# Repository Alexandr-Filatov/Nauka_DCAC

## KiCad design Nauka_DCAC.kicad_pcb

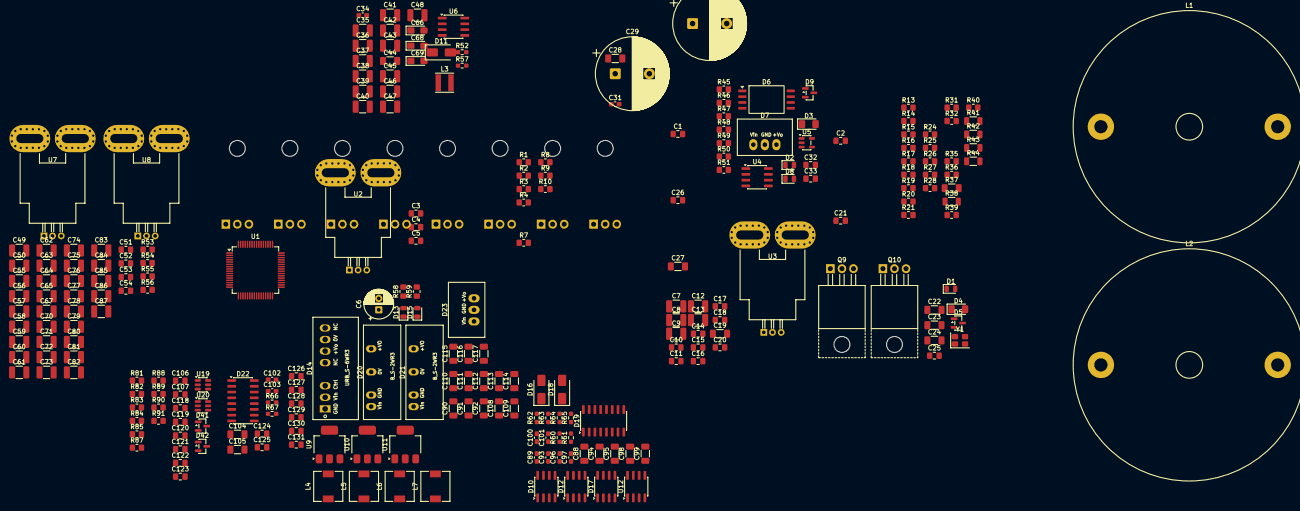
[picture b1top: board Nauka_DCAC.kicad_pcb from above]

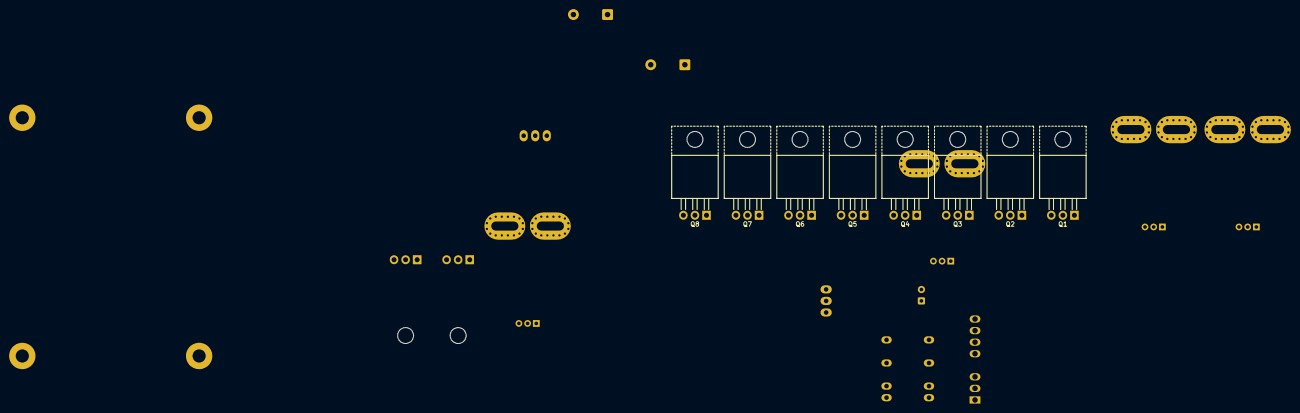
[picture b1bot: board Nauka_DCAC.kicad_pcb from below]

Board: 2 copper layers, 255 parts (8 on the bottom side), 101 nets, no tracks yet.

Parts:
C1, C2: 12p; C_0805_2012Metric_Pad1.18x1.45mm_HandSolder
C3, C11, C15, C18, C21, C32, C52, C54, C119, C121, C122, C123, C124, C125, C126, C127, C128, C129, C130, C131: 100n; C_0805_2012Metric_Pad1.18x1.45mm_HandSolder
C4, C5, C17, C20, C118, C120: 2.2u; C_0805_2012Metric_Pad1.18x1.45mm_HandSolder
C6: 47u; CP_Radial_D6.3mm_P2.50mm
C7, C8, C9, C12, C13, C35, C36, C37, C38, C39, C40, C41, C42, C43, C45, C46, C47, C48, C49, C50, C55, C56, C57, C58, C59, C60, C61, C62, C63, C64, C65, C67, C70, C71, C72, C73, C74, C75, C76, C77, C78, C79, C80, C81, C82, C83, C84, C85, C86, C87: 470n; C_1210_3225Metric_Pad1.33x2.70mm_HandSolder
C10, C14, C51, C53: 1u; C_0805_2012Metric_Pad1.18x1.45mm_HandSolder
C16, C25, C26: 56p; C_0805_2012Metric_Pad1.18x1.45mm_HandSolder
C19, C22, C44, C88, C90, C92, C94, C95, C98, C99, C104, C105, C108, C109, C110, C111, C112, C113, C114, C115, C116, C117: 10u; C_1206_3216Metric_Pad1.33x1.80mm_HandSolder
C23, C24, C27, C28: 2.2u; C_1206_3216Metric_Pad1.33x1.80mm_HandSolder
C29, C30: 1m; CP_Radial_D16.0mm_P7.50mm
C31, C34, C89, C93, C96, C97, C100, C101, C102, C103: 56p; C_0603_1608Metric_Pad1.08x0.95mm_HandSolder
C33: 1n; C_0805_2012Metric_Pad1.18x1.45mm_HandSolder
C66, C68, C69: 10u; CP_EIA-3216-18_Kemet-A_HandSolder
C91: 22u; C_1206_3216Metric_Pad1.33x1.80mm_HandSolder
C106, C107: 10p; C_0805_2012Metric_Pad1.18x1.45mm_HandSolder
D1, D2, D8, D13, D15: LED_0805_2012Metric
D3, D4: LED_1206_3216Metric_Pad1.42x1.75mm_HandSolder
D5, D9, D41, D42: SOT-23
D6: SOIC-8_7.5x5.85mm_P1.27mm
D7, D23: K78xx-500R3
D10, D12, D17: SOIC-8_3.9x4.9mm_P1.27mm
D11, D16, D18: D_SMA
D14: URB_S-6WR3
D19, D22: SOIC-16_3.9x9.9mm_P1.27mm
D20, D21: B_S-2WR3
L1, L2: L; L_Radial_D50.8mm_P38.86mm_Vishay_IHB-6
L3: 4.7u; L_Taiyo-Yuden_MD-4040
L4, L5, L6, L7: 10u; L_6.3x6.3_H3
Q1, Q2, Q3, Q4, Q5, Q6, Q7, Q8, Q9, Q10: TO-220-3_Horizontal_TabUp
R1, R2, R7, R8, R13, R14, R15, R17, R18, R24, R25, R28: 10k; R_0805_2012Metric_Pad1.20x1.40mm_HandSolder
R3, R4, R9, R10, R19, R20, R26, R27, R31, R32: 10; R_0805_2012Metric_Pad1.20x1.40mm_HandSolder
R16, R21, R46, R47, R48, R49, R58, R59, R84, R85, R90, R91: 1k; R_0805_2012Metric_Pad1.20x1.40mm_HandSolder
R35, R39, R53, R55: 2k; R_0805_2012Metric_Pad1.20x1.40mm_HandSolder
R36, R40, R54, R56: 3k; R_0805_2012Metric_Pad1.20x1.40mm_HandSolder
R37: 10k; R_1206_3216Metric_Pad1.30x1.75mm_HandSolder
R38, R41, R42, R43: 110k; R_1206_3216Metric
R44: 11.3k; R_1206_3216Metric
R45: 120; R_0805_2012Metric_Pad1.20x1.40mm_HandSolder
R50: 750; R_0805_2012Metric_Pad1.20x1.40mm_HandSolder
R51: 510; R_0805_2012Metric_Pad1.20x1.40mm_HandSolder
R52, R57, R60, R61, R62, R63, R64, R65, R66, R67: 120; R_0603_1608Metric_Pad0.98x0.95mm_HandSolder
R81, R87: 100; R_0805_2012Metric_Pad1.20x1.40mm_HandSolder
R82, R83, R88, R89: 0; R_0805_2012Metric_Pad1.20x1.40mm_HandSolder
U1: LQFP-64_10x10mm_P0.5mm
U2, U3, U7, U8: Allegro_CB_PFF
U4, U6, U12: SOIC-8_3.9x4.9mm_P1.27mm
U5: SOT-23-5
U9, U10, U11: SOT-223-3_TabPin2
U19, U20: SOT-23-6
Y1: 16M; Crystal_SMD_SeikoEpson_FA238-4Pin_3.2x2.5mm

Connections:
+3.3V: C20.2, C21.2, C32.1, C68.1, C118.1, C119.1, C120.1, C121.1, C124.2, C126.2, C128.2, C130.2, C131.2, D6.8 (VDD2), D9.2 (K), D15.2 (A), D19.1 (VDDI_1), D22.1 (DT_1), D41.2 (K), D42.2 (K), R28.1, R84.1, R90.1, U1.1 (VBAT), U1.13 (VDDA), U1.19 (VDD), U1.32 (VDD), U1.48 (VDD), U1.64 (VDD), U4.1 (VDD1), U5.5 (V+), U6.1 (VDD1), U10.2 (VO), U12.1 (VDD1), U19.4 (V+), U20.4 (V+)
+3.3VP: C17.2, C18.2, C69.1, C125.2, C127.2, C129.2, D5.2 (K), D6.1 (VDD1), D8.2 (A), U4.8 (VDD2), U6.8 (VDD2), U11.2 (VO), U12.8 (VDD2)
+5V: C10.1, C11.1, C14.1, C15.1, C51.1, C52.1, C53.1, C54.1, C66.1, D13.2 (A), U2.1 (VCC), U3.1 (VCC), U7.1 (VCC), U8.1 (VCC), U9.2 (VO)
+9V: C90.2, C92.2, D14.6 (+Vo), U9.3 (VI), U10.3 (VI)
+15V: C44.2, C94.2, C98.2, C109.2, D10.5 (VDD), D11.2 (A), D12.5 (VDD), D16.2 (A), D17.5 (VDD), D18.2 (A), D23.3 (+Vo)
+24V: C6.1, C23.2, C24.2, C27.2, C28.2, C29.1, C30.1, C110.1, C111.1, C112.1, C115.1, L1.2, L2.2, L3.1, L4.1, L5.1, L6.1, L7.1, R37.1, R38.2
/BOOT: R15.2, U1.60 (BOOT0)
/Drivers/A: C88.2, D10.6 (SW)
/Drivers/B: C95.2, D12.6 (SW)
/Drivers/C: C99.2, D17.6 (SW)
/NRST: C3.2, R28.2, U1.7 (NRST)
/OverCurrent1: C106.1, D41.3 (common), R81.1
/OverCurrent2: C107.1, D42.3 (common), R87.1
/Power/A: Q1.3 (S), Q2.2 (D), R1.2, U2.4 (IP+)
/Power/B: Q3.3 (S), Q4.2 (D), R7.2
/Power/C: Q5.3 (S), Q6.2 (D), R13.2, U3.4 (IP+)
/Power/Current_A: R35.2, R36.1
/Power/Current_C: R39.2, R40.1
/Power/Current_buck_1: R53.2, R54.1
/Power/Current_buck_2: R55.2, R56.1
/Power/DC+: C7.2, C8.2, C9.2, C12.2, C13.2, C35.2, C36.2, C37.2, C38.2, C39.2, C40.2, C41.2, C42.2, C43.2, C45.2, C46.2, C47.2, C48.2, C49.2, C50.2, C55.2, C56.2, C57.2, C58.2, C59.2, C60.2, C61.2, C62.2, C63.2, C64.2, C65.2, C67.2, C70.2, C71.2, C72.2, C73.2, C74.2, C75.2, C76.2, C77.2, C78.2, C79.2, C80.2, C81.2, C82.2, C83.2, C84.2, C85.2, C86.2, C87.2, Q1.2 (D), Q3.2 (D), Q5.2 (D), Q7.2 (D), Q8.2 (D)
/Power/GH1: Q1.1 (G), R1.1, R3.1
/Power/GH2: Q3.1 (G), R7.1, R9.1
/Power/GH3: Q5.1 (G), R13.1, R19.1
/Power/GH4: Q7.1 (G), R17.1, R26.1
/Power/GH4_ON: R26.2, R31.2
/Power/GH5: Q8.1 (G), R24.1, R31.1
/Power/GL1: Q2.1 (G), R2.1, R4.1
/Power/GL2: Q4.1 (G), R8.1, R10.1
/Power/GL3: Q6.1 (G), R14.1, R20.1
/Power/GL4: Q9.1 (G), R18.1, R27.1
/Power/GL5: Q10.1 (G), R25.1, R32.1
/Power/S1: Q7.3 (S), Q9.2 (D), R17.2, U7.4 (IP+)
/Power/S2: Q8.3 (S), Q10.2 (D), R24.2, U8.4 (IP+)
/Power/Voltage_MCU: C33.2, D9.3 (common), R51.2
/SHDN_OverCurrent_1: R82.2, U19.6 (SHDN)
/SHDN_OverCurrent_2: R88.2, U20.6 (SHDN)
GND: C1.1, C2.2, C3.1, C4.2, C5.2, C10.2, C11.2, C14.2, C15.2, C20.1, C21.1, C25.2, C32.2, C33.1, C51.2, C52.2, C53.2, C54.2, C66.2, C68.2, C90.1, C92.1, C100.2, C101.1, C102.2, C103.1, C106.2, C107.2, C118.2, C119.2, C120.2, C121.2, C122.2, C123.2, C124.1, C126.1, C128.1, C130.1, C131.1, D6.5 (GND2), D9.1 (A), D14.7 (0V), D41.1 (A), D42.1 (A), R15.1, R16.2, R21.2, R36.2, R40.2, R48.2, R54.2, R56.2, R58.2, R59.2, R82.1, R85.2, R88.1, R91.2, U1.12 (VSSA), U1.18 (VSS), U1.63 (VSS), U2.2 (GND), U3.2 (GND), U4.4 (GND1), U5.2 (V-), U6.4 (GND1), U7.2 (GND), U8.2 (GND), U9.1 (GND), U10.1 (GND), U12.4 (GND1), U19.2 (V-), U20.2 (V-), Y1.2, Y1.4
GNDPWR: C6.2, C7.1, C8.1, C9.1, C12.1, C13.1, C17.1, C18.1, C19.1, C22.1, C23.1, C24.1, C27.1, C28.1, C29.2, C30.2, C31.1, C34.2, C35.1, C36.1, C37.1, C38.1, C39.1, C40.1, C41.1, C42.1, C43.1, C44.1, C45.1, C46.1, C47.1, C48.1, C49.1, C50.1, C55.1, C56.1, C57.1, C58.1, C59.1, C60.1, C61.1, C62.1, C63.1, C64.1, C65.1, C67.1, C69.2, C70.1, C71.1, C72.1, C73.1, C74.1, C75.1, C76.1, C77.1, C78.1, C79.1, C80.1, C81.1, C82.1, C83.1, C84.1, C85.1, C86.1, C87.1, C89.1, C91.1, C93.2, C94.1, C96.1, C97.2, C98.1, C108.1, C109.1, C110.2, C111.2, C112.2, C113.1, C115.2, C116.1, C125.1, C127.1, C129.1, D7.2 (GND), D10.3 (GND), D12.3 (GND), D14.1 (GND), D17.3 (GND), D20.2 (GND), D21.2 (GND), D23.2 (GND), Q2.3 (S), Q4.3 (S), Q6.3 (S), Q9.3 (S), Q10.3 (S), R2.2, R8.2, R14.2, R18.2, R25.2, R50.2, U4.5 (GND2), U6.5 (GND2), U11.1 (GND), U12.5 (GND2)
unnamed: C26.1, R49.1, R51.1, U5.1
unnamed: D1.2 (A), U1.2 (PC13)
unnamed: D1.1 (K), R16.1
unnamed: D2.2 (A), U1.3 (PC14)
unnamed: D2.1 (K), R21.1
unnamed: C16.1, D3.2 (A), D4.1 (K), D6.3 (SHTDN), D6.4 (GND1), R44.1
unnamed: D3.1 (K), D4.2 (A), R37.2
unnamed: C16.2, D5.3 (common), D6.2 (VIN), R45.2
unnamed: D6.6 (OUTN), R47.1
unnamed: D6.7 (OUTP), R46.1
unnamed: C22.2, D7.3 (+Vo), U11.3 (VI)
unnamed: C19.2, D7.1 (Vin), L5.2
unnamed: D8.1 (K), R50.1
unnamed: C88.1, D10.8 (BST), D11.1 (K)
unnamed: C31.2, D10.1 (HI), R52.2
unnamed: C34.1, D10.2 (LI), R57.2
unnamed: C95.1, D12.8 (BST), D16.1 (K)
unnamed: C89.2, D12.1 (HI), R60.2
unnamed: C93.1, D12.2 (LI), R61.2
unnamed: D13.1 (K), R58.1
unnamed: C91.2, D14.2 (Vin), L3.2
unnamed: D15.1 (K), R59.1
unnamed: C99.1, D17.8 (BST), D18.1 (K)
unnamed: C96.2, D17.1 (HI), R62.2
unnamed: C97.1, D17.2 (LI), R63.2
unnamed: C101.2, R65.2
unnamed: C100.1, R64.2
unnamed: C114.1, D20.4 (0V)
unnamed: C114.2, D20.6 (+Vo)
unnamed: C113.2, D20.1 (Vin), L6.2
unnamed: C117.1, D21.4 (0V)
unnamed: C117.2, D21.6 (+Vo)
unnamed: C116.2, D21.1 (Vin), L7.2
unnamed: C103.2, R67.2
unnamed: C102.1, R66.2
unnamed: C108.2, D23.1 (Vin), L4.2
unnamed: R38.1, R41.2
unnamed: R41.1, R42.2
unnamed: R42.1, R43.2
unnamed: R43.1, R44.2, R45.1
unnamed: R81.2, U19.5
unnamed: R87.2, U20.5
unnamed: C1.2, U1.5 (PH0), Y1.3
unnamed: C2.1, U1.6 (PH1), Y1.1
unnamed: C4.1, U1.31 (VCAP_1)
unnamed: C5.1, U1.47 (VCAP_2)
unnamed: R35.1, U2.3 (VIOUT)
unnamed: R39.1, U3.3 (VIOUT)
unnamed: R52.1, U4.7 (VOA)
unnamed: R57.1, U4.6 (VOB)
unnamed: C25.1, R46.2, R48.1, U5.3 (+)
unnamed: C26.2, R47.2, R49.2, U5.4 (-)
unnamed: R60.1, U6.7 (VOA)
unnamed: R61.1, U6.6 (VOB)
unnamed: L1.1, U7.5 (IP-)
unnamed: R53.1, U7.3 (VIOUT)
unnamed: L2.1, U8.5 (IP-)
unnamed: R55.1, U8.3 (VIOUT)
unnamed: R62.1, U12.7 (VOA)
unnamed: R63.1, U12.6 (VOB)
unnamed: C122.1, R83.2, R84.2, R85.1, U19.1 (-)
unnamed: C123.1, R89.2, R90.2, R91.1, U20.1 (-)

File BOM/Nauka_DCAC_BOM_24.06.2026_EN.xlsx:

Reference | Value | Product Name | Replacement | Package | Description | Quantity | DNP
C3, C11, C15, C18, C21, C32, C52, C54, C119, C121, C122, C123, C124, C125, C126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 | 100n |  |  | SMD 0805 | Capacitor SMD 25V | 20
C106, C107 | 10p |  |  | SMD 0805 | Capacitor SMD 25V | 2
C66, C68, C69 | 10u |  |  | CP EIA-3216-18 Kemet-A | Capacitor tantalum SMD 10V | 3
C19, C22, C44, C88, C90, C92, C94, C95, C98, C99, C104, C105, C108, C109, C110,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 | 10u |  |  | SMD 1206 | Capacitor SMD 50V | 22
C1, C2 | 12p |  |  | SMD 0805 | Capacitor SMD 25V | 2
C29, C30 | 1m | EXR102M63B |  | CP Radial D16.0mm P7.50mm | Capacitor electrolytic low ESR | 2
C33 | 1n |  |  | SMD 0805 | Capacitor SMD 25V | 1
C10, C14, C51, C53 | 1u |  |  | SMD 0805 | Capacitor SMD 25V | 4
C4, C5, C17, C20, C118, C120 | 2.2u |  |  | SMD 0805 | Capacitor SMD 25V | 6
C23, C24, C27, C28 | 2.2u |  |  | SMD 1206 | Capacitor SMD 50V | 4
C91 | 22u |  |  | SMD 1206 | Capacitor SMD 50V | 1
C7, C8, C9, C12, C13, C35, C36, C37, C38, C39, C40, C41, C42, C43, C45, C46, C4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 | 470n | 1210B474K201CT |  | SMD 1210 | Capacitor SMD 200V | 50
C6 | 47u | EEUFR1J470 |  | CP Radial D6.3mm P2.50mm | Capacitor electrolytic low ESR | 1
C31, C34, C89, C93, C96, C97, C100, C101, C102, C103 | 56p |  |  | SMD 0603 | Capacitor SMD 25V | 10
C16, C25, C26 | 56p |  |  | SMD 0805 | Capacitor SMD 25V | 3
D7 | ~ | K7805-500R3 |  | K78xx-500R3 | DC/DC | 1
D23 | ~ | K7815-500R3 |  | K78xx-500R3 | DC/DC | 1
D20, D21 | ~ | B2415S-2WR3 |  | S-2WR3 | DC/DC | 2
D11, D16, D18 | ~ | ES1D-E3/61T |  | SMA | Ultrafast diode | 3
D1, D2 | ~ | FYLS-0603UBC |  | SMD 0805 | Blue LED | 2
D8, D13, D15 | ~ | FYLS-0805UYC |  | SMD 0805 | Yellow LED | 3
D4 | ~ | TO-3216BC-PG |  | SMD 1206 | Green LED | 1
D3 | ~ | TO-3216BC-MRE |  | SMD 1206 | Red LED | 1
D19, D22 | ~ | NSI6602 |  | SOIC-16 3.9x9.9mm P1.27mm | Gate driver | 2
D10, D12, D17 | ~ | NSD1624 |  | SOIC-8 3.9x4.9mm P1.27mm | Gate driver | 3
D6 | ~ | NSI1311 |  | SOIC-8 7.5x5.85mm P1.27mm | Isolated amplifier | 1
D5, D9, D41, D42 | ~ | BAT54S |  | SOT-23 | Schottky barrier diode | 4
D14 | ~ | URB_S-6WR3 |  | URB S-6WR3 | DC/DC | 1
L4, L5, L6, L7 | 10u | LQH66SN100M03L |  | 6.3x6.3 H3 | Inductor SMD | 4
L3 | 4.7u | LQH44PN4R7MP0L |  | Taiyo-Yuden MD-4040 | Inductor SMD | 1
Q1, Q2, Q3, Q4, Q5, Q6, Q7, Q8, Q9, Q10 | ~ | WMK115N15HG2 |  | TO-220-3 | MOSFET | 10
R82, R83, R88, R89 | 0 |  |  | SMD 0805 | Resistor SMD 1% | 4 | ✓
R3, R4, R9, R10, R19, R20, R26, R27, R31, R32 | 10 |  |  | SMD 0805 | Resistor SMD 1% | 10
R81, R87 | 100 |  |  | SMD 0805 | Resistor SMD 1% | 2
R1, R2, R7, R8, R13, R14, R15, R17, R18, R24, R25, R28 | 10k |  |  | SMD 0805 | Resistor SMD 1% | 12
R37 | 10k |  |  | SMD 1206 | Resistor SMD 1% | 1
R44 | 11.3k |  |  | SMD 1206 | Resistor SMD 0.1% | 1
R38, R41, R42, R43 | 110k |  |  | SMD 1206 | Resistor SMD 0.1% | 4
R52, R57, R60, R61, R62, R63, R64, R65, R66, R67 | 120 |  |  | SMD 0603 | Resistor SMD 1% | 10
R45 | 120 |  |  | SMD 0805 | Resistor SMD 1% | 1
R16, R21, R46, R47, R48, R49, R58, R59, R84, R85, R90, R91 | 1k |  |  | SMD 0805 | Resistor SMD 1% | 12
R35, R39, R53, R55 | 2k |  |  | SMD 0805 | Resistor SMD 0.1% | 4
R36, R40, R54, R56 | 3k |  |  | SMD 0805 | Resistor SMD 0.1% | 4
R51 | 510 |  |  | SMD 0805 | Resistor SMD 1% | 1
R50 | 750 |  |  | SMD 0805 | Resistor SMD 1% | 1
U2, U3, U7, U8 | ~ | CH704150CT |  | Allegro CB PFF | Current sensor | 4
U1 | ~ | STM32F405RGTx |  | LQFP-64 10x10mm P0.5mm | MCU | 1
U4, U6, U12 | ~ | NSI8220 |  | SOIC-8 3.9x4.9mm P1.27mm | Digital isolator | 3
U10, U11 | ~ | AMS1117-3.3 |  | SOT-223-3 | Linear regulator | 2
U9 | ~ | AMS1117-5.0 |  | SOT-223-3 | Linear regulator | 1
U5 | ~ | OPA333xxDBV |  | SOT-23-5 | Op-Amp | 1
U19, U20 | ~ | TLV3501AIDBV |  | SOT-23-6 | Comparator | 2
Y1 | 16M | X322516MOB4SI |  | Crystal SMD SeikoEpson FA238-4Pin 3.2x2.5mm | Crystal | 1

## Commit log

2026-06-22 zero commit
2026-06-23 VER1.0: собрал силовую часть на схеме
2026-06-23 VER1.0: добавил драйвера и все питание схемы
2026-06-24 VER1.0: составил список примерно 95% компонентов
